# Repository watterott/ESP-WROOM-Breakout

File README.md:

# ESP-WROOM-Breakout
Breakouts for ESP8266 and ESP32 WiFi/WLAN + Bluetooth modules from Espressif.

* [Espressif ESP8266EX ESP-WROOM-02](https://espressif.com/en/products/hardware/esp8266ex/overview) WiFi module
* [Espressif ESP32 ESP-WROOM-32](https://espressif.com/en/products/hardware/esp32/overview) WiFi+Bluetooth module
* Silabs CP2102N USB UART Bridge (up to 3M baud)
* microUSB-Connector
* Open-Source and released under the [Creative Commons Attribution Share-Alike License](https://creativecommons.org/licenses/by-sa/4.0/).
* **[Documentation on learn.watterott.com](https://learn.watterott.com)**

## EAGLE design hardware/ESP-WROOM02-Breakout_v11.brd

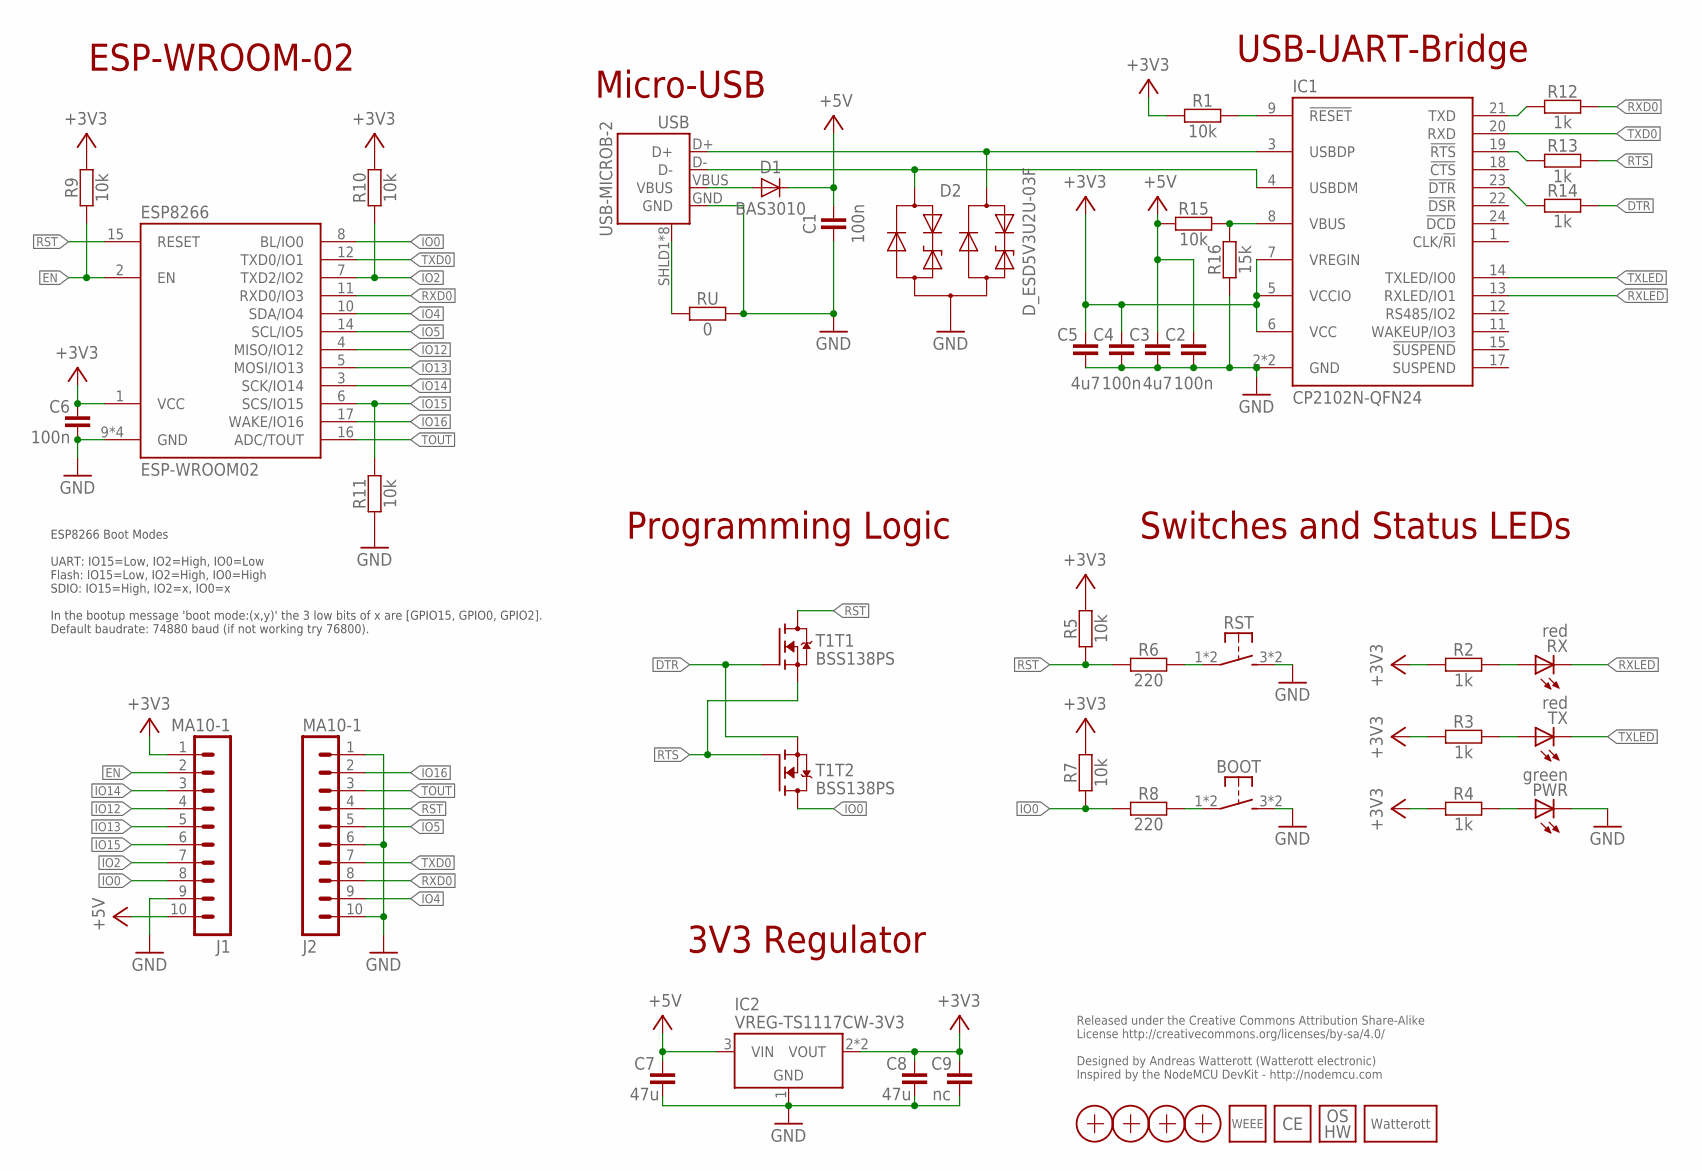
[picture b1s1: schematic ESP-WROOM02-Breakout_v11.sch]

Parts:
BOOT: SW-TACTILE-PTS840P; PTS840P
C1, C2, C4, C6: 100n; C0402
C3, C5: 4u7; C0603
C7, C8: 47u; C1206
C9: nc; C1206
D1: BAS3010; SOD323
D2: D_ESD5V3U2U-03F; SOT723
ESP8266: ESP-WROOM02
IC1: CP2102N-QFN24; QFN24-PAD
IC2: VREG-TS1117CW-3V3; SOT223
J1, J2: MA10-1
LOGO1: LOGO_SPARK-4; SPARK_4MM
LOGO2: LOGO_OSHW-2; OSHW_2MM
LOGO3: LOGO_WEEE-4; WEEE_4MM
LOGO4: LOGO_CE-2; CE_2MM
PWR: green; C0603
R1, R5, R7, R9, R10, R11, R15: 10k; C0402
R2, R3, R4, R12, R13, R14: 1k; C0402
R6, R8: 220; C0402
R16: 15k; C0402
RST: SW-TACTILE-PTS840P; PTS840P
RU: 0; C0402
RX: red; C0603
T1: BSS138PS; SOT363
TX: red; C0603
USB: USB-MICROB-2; USB-MICROB-10118194
X1, X2, X3, X4: PASSER-07; PASSER_07MM

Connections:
+3V3: C4.2, C5.2, C6.2, C8.2, C9.2, ESP8266.1 (VCC), IC1.5 (VCCIO), IC1.6 (VCC), IC1.7 (VREGIN), IC2.2 (VOUT), IC2.4 (VOUT), J1.1, R1.1, R2.1, R3.1, R4.1, R5.2, R7.2, R9.2, R10.2
+5V: C1.2, C2.2, C3.2, C7.2, D1.C, IC2.3 (VIN), J1.10, R15.1
CPDTR: IC1.23 (!DTR), R14.1
CPRTS: IC1.19 (!RTS), R13.1
CPTX: IC1.21 (TXD), R12.1
CP_VBUS: IC1.8 (VBUS), R15.2, R16.2
DTR: R14.2, T1.2 (G), T1.4 (S)
D_N: D2.1 (C1), IC1.4 (USBDM), USB.D-
D_P: D2.2 (C2), IC1.3 (USBDP), USB.D+
EN: ESP8266.2 (EN), J1.2, R9.1
GND: BOOT.3 (S1), BOOT.4 (S1), C1.1, C2.1, C3.1, C4.1, C5.1, C6.1, C7.1, C8.1, C9.1, D2.3 (A), ESP8266.9 (GND), ESP8266.13 (GND), ESP8266.18 (GND), ESP8266.TP (GND), IC1.2 (GND), IC1.TP (GND), IC2.1 (GND), J1.9, J2.1, J2.6, J2.10, PWR.C, R11.1, R16.1, RST.3 (S1), RST.4 (S1), RU.2, USB.GND
IO0: ESP8266.8 (BL/IO0), J1.8, R7.1, R8.1, T1.3 (D)
IO2: ESP8266.7 (TXD2/IO2), J1.7, R10.1
IO4: ESP8266.10 (SDA/IO4), J2.9
IO5: ESP8266.14 (SCL/IO5), J2.5
IO12: ESP8266.4 (MISO/IO12), J1.4
IO13: ESP8266.5 (MOSI/IO13), J1.5
IO14: ESP8266.3 (SCK/IO14), J1.3
IO15: ESP8266.6 (SCS/IO15), J1.6, R11.2
IO16: ESP8266.17 (WAKE/IO16), J2.2
unnamed: R6.2, RST.1, RST.2 (P1)
unnamed: BOOT.1, BOOT.2 (P1), R8.2
PWR-LED: PWR.A, R4.2
RESET: IC1.9 (!RESET), R1.2
RST: ESP8266.15 (RESET), J2.4, R5.1, R6.1, T1.6 (D)
RTS: R13.2, T1.1 (S), T1.5 (G)
RX-LED: R2.2, RX.A
RXD0: ESP8266.11 (RXD0/IO3), J2.8, R12.2
RXLED: IC1.13 (RXLED/IO1), RX.C
SHLD: RU.1, USB.SHLD1 (SHIELD), USB.SHLD2 (SHIELD), USB.SHLD3 (SHIELD), USB.SHLD4 (SHIELD), USB.SHLD5 (SHIELD), USB.SHLD6 (SHIELD), USB.SHLD7 (SHIELD), USB.SHLD8 (SHIELD)
TOUT: ESP8266.16 (ADC/TOUT), J2.3
TX-LED: R3.2, TX.A
TXD0: ESP8266.12 (TXD0/IO1), IC1.20 (RXD), J2.7
TXLED: IC1.14 (TXLED/IO0), TX.C
VBUS: D1.A, USB.VBUS

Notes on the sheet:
Released under the Creative Commons Attribution Share-Alike License http://creativecommons.org/licenses/by-sa/4.0/ Designed by Andreas Watterott (Watterott electronic) Inspired by the NodeMCU DevKit - http://nodemcu.com
USB-UART-Bridge
Micro-USB
Switches and Status LEDs
Programming Logic
ESP-WROOM-02
ESP8266 Boot Modes UART: IO15=Low, IO2=High, IO0=Low Flash: IO15=Low, IO2=High, IO0=High SDIO: IO15=High, IO2=x, IO0=x In the bootup message 'boot mode:(x,y)' the 3 low bits of x are [GPIO15, GPIO0, GPIO2]. Default baudrate: 74880 baud (if not working try 76800).
3V3 Regulator

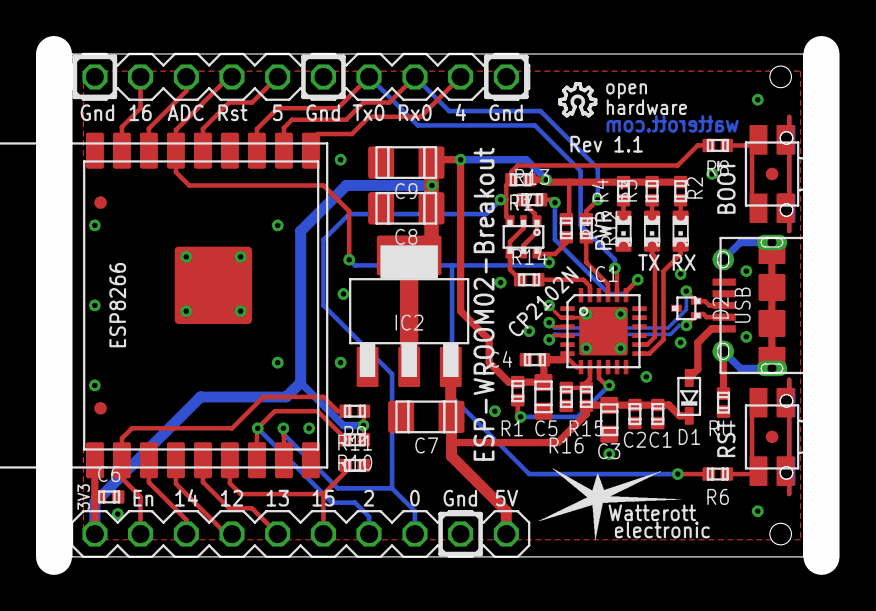
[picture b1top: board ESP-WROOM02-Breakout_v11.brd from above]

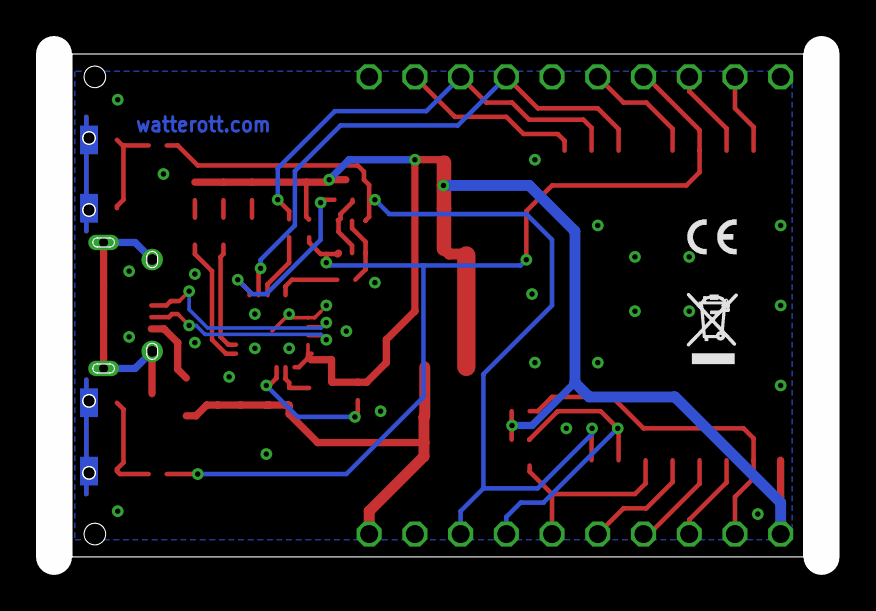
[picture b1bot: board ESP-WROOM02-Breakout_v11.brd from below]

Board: 2 copper layers, 42.6 x 27.9 mm, 48 parts (2 on the bottom side), 35 nets.

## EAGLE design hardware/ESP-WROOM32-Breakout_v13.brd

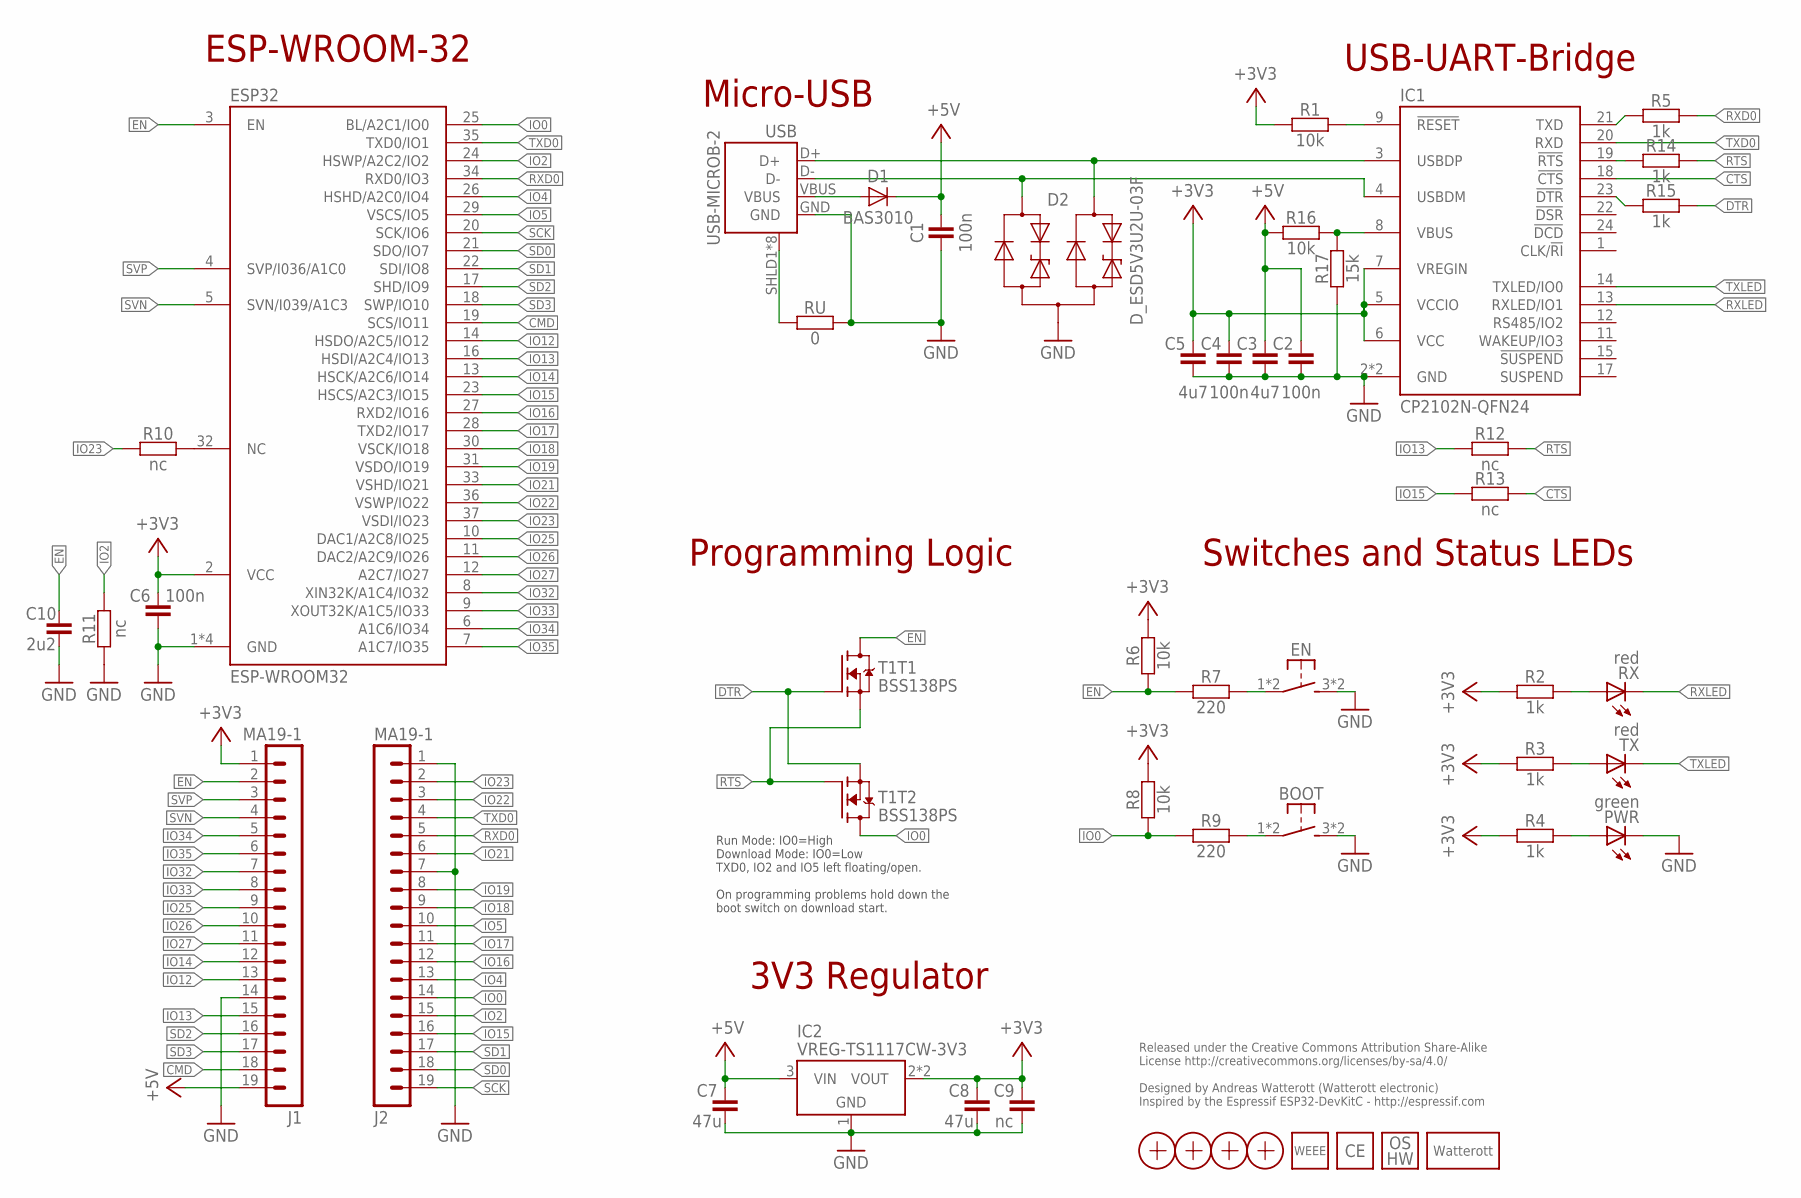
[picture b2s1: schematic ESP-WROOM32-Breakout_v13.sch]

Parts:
BOOT: SW-TACTILE-PTS840P; PTS840P
C1, C2, C4, C6: 100n; C0402
C3, C5: 4u7; C0603
C7, C8: 47u; C1206
C9: nc; C1206
C10: 2u2; C0402
D1: BAS3010; SOD323
D2: D_ESD5V3U2U-03F; SOT723
EN: SW-TACTILE-PTS840P; PTS840P
ESP32: ESP-WROOM32
IC1: CP2102N-QFN24; QFN24-PAD
IC2: VREG-TS1117CW-3V3; SOT223
J1, J2: MA19-1
LOGO1: LOGO_SPARK-4; SPARK_4MM
LOGO2: LOGO_OSHW-2; OSHW_2MM
LOGO3: LOGO_CE-2; CE_2MM
LOGO4: LOGO_WEEE-4; WEEE_4MM
PWR: green; C0603
R1, R6, R8, R16: 10k; C0402
R2, R3, R4, R5, R14, R15: 1k; C0402
R7, R9: 220; C0402
R10, R11, R12, R13: nc; C0402
R17: 15k; C0402
RU: 0; C0402
RX: red; C0603
T1: BSS138PS; SOT363
TX: red; C0603
USB: USB-MICROB-2; USB-MICROB-10118194
X1, X2, X3, X4: PASSER-07; PASSER_07MM

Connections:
+3V3: C4.2, C5.2, C6.2, C8.2, C9.2, ESP32.2 (VCC), IC1.5 (VCCIO), IC1.6 (VCC), IC1.7 (VREGIN), IC2.2 (VOUT), IC2.4 (VOUT), J1.1, R1.1, R2.1, R3.1, R4.1, R6.2, R8.2
+5V: C1.2, C2.2, C3.2, C7.2, D1.C, IC2.3 (VIN), J1.19, R16.1
CMD: ESP32.19 (SCS/IO11), J1.18
CPDTR: IC1.23 (!DTR), R15.1
CPRTS: IC1.19 (!RTS), R14.1
CPTX: IC1.21 (TXD), R5.1
CP_VBUS: IC1.8 (VBUS), R16.2, R17.2
CTS: IC1.18 (!CTS), R13.2
DTR: R15.2, T1.2 (G), T1.4 (S)
D_N: D2.1 (C1), IC1.4 (USBDM), USB.D-
D_P: D2.2 (C2), IC1.3 (USBDP), USB.D+
EN: C10.2, ESP32.3 (EN), J1.2, R6.1, R7.1, T1.6 (D)
GND: BOOT.3 (S1), BOOT.4 (S1), C1.1, C2.1, C3.1, C4.1, C5.1, C6.1, C7.1, C8.1, C9.1, C10.1, D2.3 (A), EN.3 (S1), EN.4 (S1), ESP32.1 (GND), ESP32.15 (GND), ESP32.38 (GND), ESP32.TP (GND), IC1.2 (GND), IC1.TP (GND), IC2.1 (GND), J1.14, J2.1, J2.7, PWR.C, R11.1, R17.1, RU.2, USB.GND
IO0: ESP32.25 (BL/A2C1/IO0), J2.14, R8.1, R9.1, T1.3 (D)
IO2: ESP32.24 (HSWP/A2C2/IO2), J2.15, R11.2
IO4: ESP32.26 (HSHD/A2C0/IO4), J2.13
IO5: ESP32.29 (VSCS/IO5), J2.10
IO12: ESP32.14 (HSDO/A2C5/IO12), J1.13
IO13: ESP32.16 (HSDI/A2C4/IO13), J1.15, R12.1
IO14: ESP32.13 (HSCK/A2C6/IO14), J1.12
IO15: ESP32.23 (HSCS/A2C3/IO15), J2.16, R13.1
IO16: ESP32.27 (RXD2/IO16), J2.12
IO17: ESP32.28 (TXD2/IO17), J2.11
IO18: ESP32.30 (VSCK/IO18), J2.9
IO19: ESP32.31 (VSDO/IO19), J2.8
IO21: ESP32.33 (VSHD/IO21), J2.6
IO22: ESP32.36 (VSWP/IO22), J2.3
IO23: ESP32.37 (VSDI/IO23), J2.2, R10.1
IO25: ESP32.10 (DAC1/A2C8/IO25), J1.9
IO26: ESP32.11 (DAC2/A2C9/IO26), J1.10
IO27: ESP32.12 (A2C7/IO27), J1.11
IO32: ESP32.8 (XIN32K/A1C4/IO32), J1.7
IO33: ESP32.9 (XOUT32K/A1C5/IO33), J1.8
IO34: ESP32.6 (A1C6/IO34), J1.5
IO35: ESP32.7 (A1C7/IO35), J1.6
unnamed: EN.1, EN.2 (P1), R7.2
unnamed: BOOT.1, BOOT.2 (P1), R9.2
NC: ESP32.32 (NC), R10.2
PWR-LED: PWR.A, R4.2
RESET: IC1.9 (!RESET), R1.2
RTS: R12.2, R14.2, T1.1 (S), T1.5 (G)
RX-LED: R2.2, RX.A
RXD0: ESP32.34 (RXD0/IO3), J2.5, R5.2
RXLED: IC1.13 (RXLED/IO1), RX.C
SCK: ESP32.20 (SCK/IO6), J2.19
SD0: ESP32.21 (SDO/IO7), J2.18
SD1: ESP32.22 (SDI/IO8), J2.17
SD2: ESP32.17 (SHD/IO9), J1.16
SD3: ESP32.18 (SWP/IO10), J1.17
SHLD: RU.1, USB.SHLD1 (SHIELD), USB.SHLD2 (SHIELD), USB.SHLD3 (SHIELD), USB.SHLD4 (SHIELD), USB.SHLD5 (SHIELD), USB.SHLD6 (SHIELD), USB.SHLD7 (SHIELD), USB.SHLD8 (SHIELD)
SVN: ESP32.5 (SVN/I039/A1C3), J1.4
SVP: ESP32.4 (SVP/I036/A1C0), J1.3
TX-LED: R3.2, TX.A
TXD0: ESP32.35 (TXD0/IO1), IC1.20 (RXD), J2.4
TXLED: IC1.14 (TXLED/IO0), TX.C
VBUS: D1.A, USB.VBUS

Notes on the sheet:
Released under the Creative Commons Attribution Share-Alike License http://creativecommons.org/licenses/by-sa/4.0/ Designed by Andreas Watterott (Watterott electronic) Inspired by the Espressif ESP32-DevKitC - http://espressif.com
USB-UART-Bridge
Micro-USB
Switches and Status LEDs
Programming Logic
ESP-WROOM-32
3V3 Regulator
Run Mode: IO0=High Download Mode: IO0=Low TXD0, IO2 and IO5 left floating/open. On programming problems hold down the boot switch on download start.

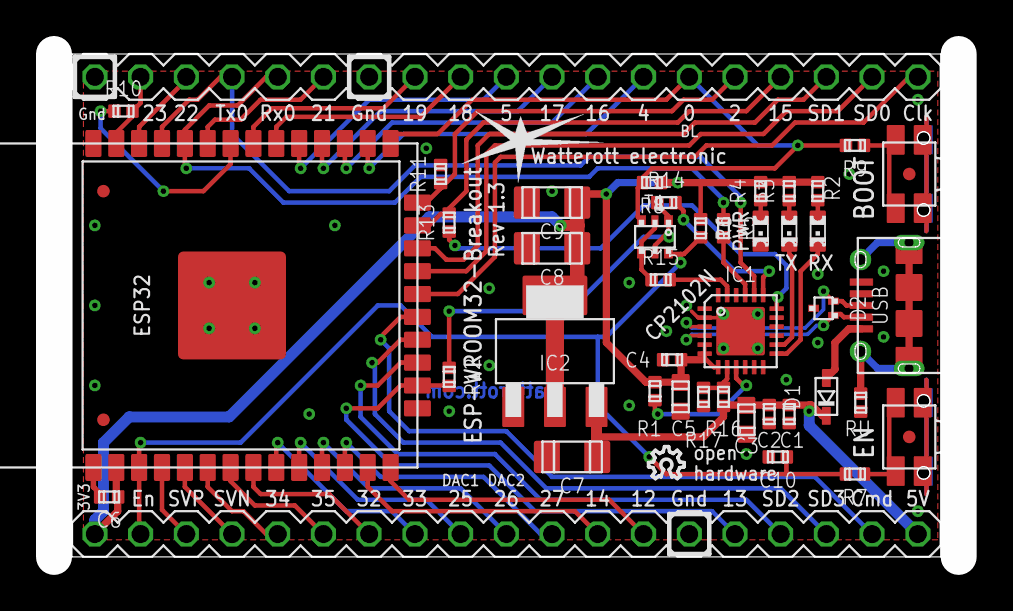
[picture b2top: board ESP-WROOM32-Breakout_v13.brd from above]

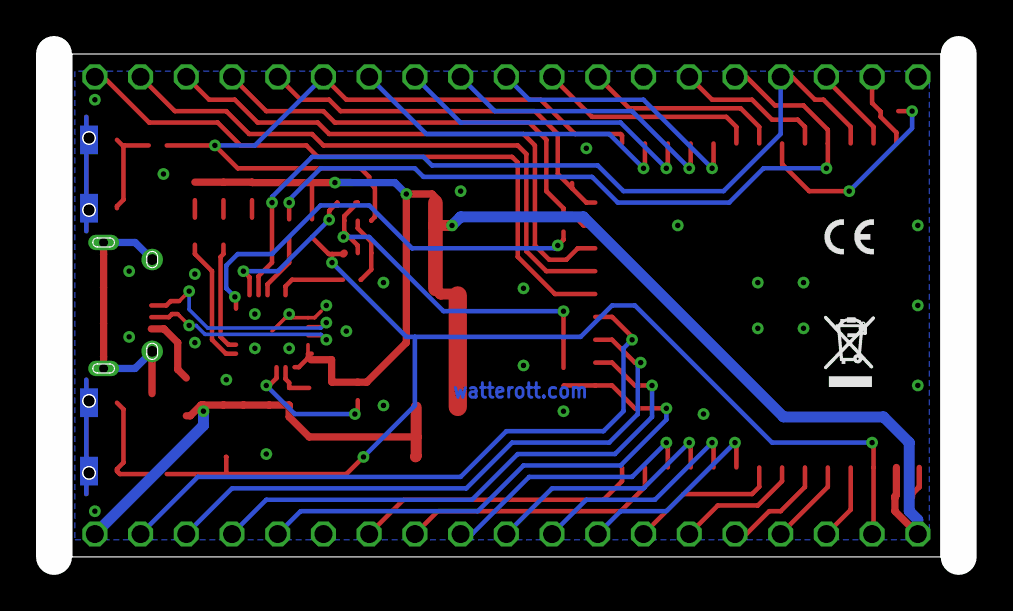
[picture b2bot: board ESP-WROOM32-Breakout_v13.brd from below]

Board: 2 copper layers, 50.3 x 27.9 mm, 50 parts (2 on the bottom side), 56 nets.

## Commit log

2018-04-27 added rev 1.2
2018-10-27 added rev 1.3
2019-03-23 added WROOM02 rev 1.1
